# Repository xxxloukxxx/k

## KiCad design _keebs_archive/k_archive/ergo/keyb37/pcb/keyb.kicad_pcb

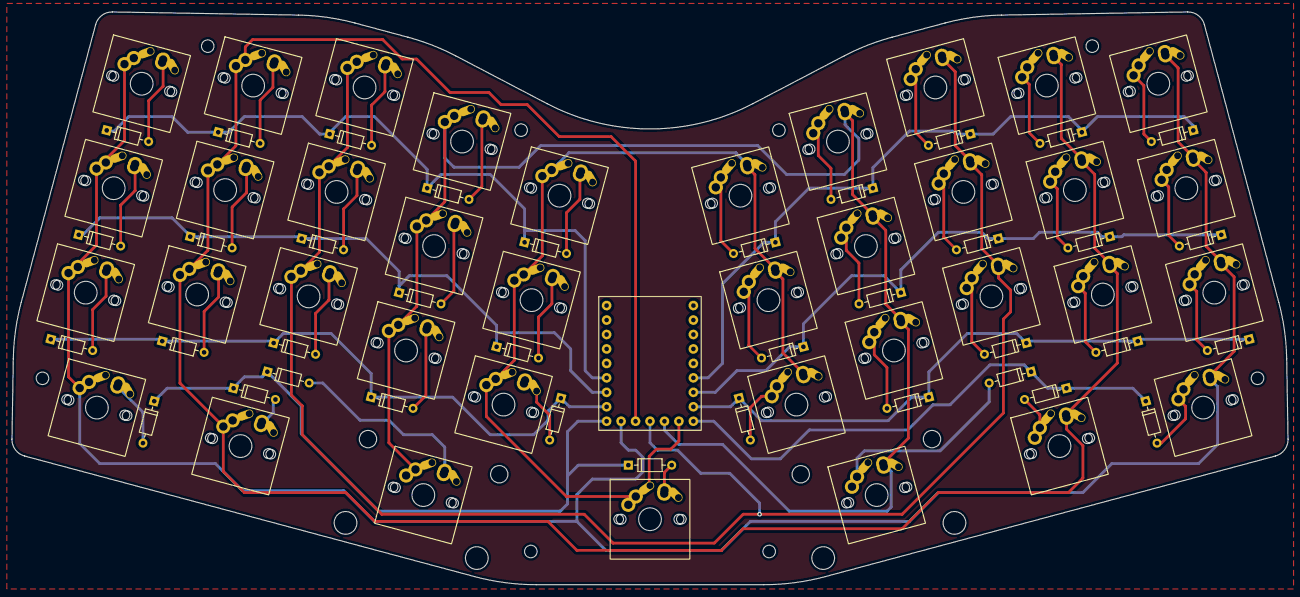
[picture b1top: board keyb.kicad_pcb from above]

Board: 2 copper layers, 224.2 x 100.6 mm, 83 parts (0 on the bottom side), 50 nets.

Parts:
D1, D2, D3, D4, D5, D6, D7, D8, D9, D10, D11, D12, D13, D14, D15, D16, D17, D18, D19, D20, D21, D22, D23, D24, D25, D26, D27, D28, D29, D30, D31, D32, D33, D34, D35, D36, D37: Diode
H1, H2, H3, H4, H5, H6, H7, H8: MountingHole; MountingHole_2.2mm_M2
SW1, SW2, SW3, SW4, SW5, SW6, SW7, SW8, SW9, SW10, SW11, SW12, SW13, SW14, SW15, SW16, SW17, SW18, SW19, SW20, SW21, SW22, SW23, SW24, SW25, SW26, SW27, SW28, SW29, SW30, SW31, SW32, SW34, SW36, SW37: key; MX-5pin
SW33, SW35: key; MX-5pin_stab
U1: RP2040

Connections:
C1: SW1.1, SW10.2, SW11.1, SW20.2, SW21.1, SW30.2, SW31.1, SW37.2, U1.13
C2: SW2.1, SW9.2, SW12.1, SW19.2, SW22.1, SW29.2, SW32.1, SW36.2, U1.12
C3: SW3.1, SW8.2, SW13.1, SW18.2, SW23.1, SW28.2, U1.11
C4: SW4.1, SW7.2, SW14.1, SW17.2, SW24.1, SW27.2, SW33.1, SW35.2, U1.10
C5: SW5.1, SW6.2, SW15.1, SW16.2, SW25.1, SW26.2, SW34.1, U1.9
L1: D1.1, D2.1, D3.1, D4.1, D5.1, U1.17
L2: D11.1, D12.1, D13.1, D14.1, D15.1, U1.16
L3: D21.1, D22.1, D23.1, D24.1, D25.1, U1.15
L4: D31.1, D32.1, D33.1, D34.1, U1.14
L5: D35.1, D36.1, D37.1, U1.8
L6: D26.1, D27.1, D28.1, D29.1, D30.1, U1.7
L7: D16.1, D17.1, D18.1, D19.1, D20.1, U1.6
L8: D6.1, D7.1, D8.1, D9.1, D10.1, U1.5
unnamed: D1.2, SW1.2
unnamed: D2.2, SW2.2
unnamed: D3.2, SW3.2
unnamed: D4.2, SW4.2
unnamed: D5.2, SW5.2
unnamed: D6.2, SW6.1
unnamed: D7.2, SW7.1
unnamed: D8.2, SW8.1
unnamed: D9.2, SW9.1
unnamed: D10.2, SW10.1
unnamed: D11.2, SW11.2
unnamed: D12.2, SW12.2
unnamed: D13.2, SW13.2
unnamed: D14.2, SW14.2
unnamed: D15.2, SW15.2
unnamed: D16.2, SW16.1
unnamed: D17.2, SW17.1
unnamed: D18.2, SW18.1
unnamed: D19.2, SW19.1
unnamed: D20.2, SW20.1
unnamed: D21.2, SW21.2
unnamed: D22.2, SW22.2
unnamed: D23.2, SW23.2
unnamed: D24.2, SW24.2
unnamed: D25.2, SW25.2
unnamed: D26.2, SW26.1
unnamed: D27.2, SW27.1
unnamed: D28.2, SW28.1
unnamed: D29.2, SW29.1
unnamed: D30.2, SW30.1
unnamed: D31.2, SW31.2
unnamed: D32.2, SW32.2
unnamed: D33.2, SW33.2
unnamed: D34.2, SW34.2
unnamed: D35.2, SW35.1
unnamed: D36.2, SW36.1
unnamed: D37.2, SW37.1

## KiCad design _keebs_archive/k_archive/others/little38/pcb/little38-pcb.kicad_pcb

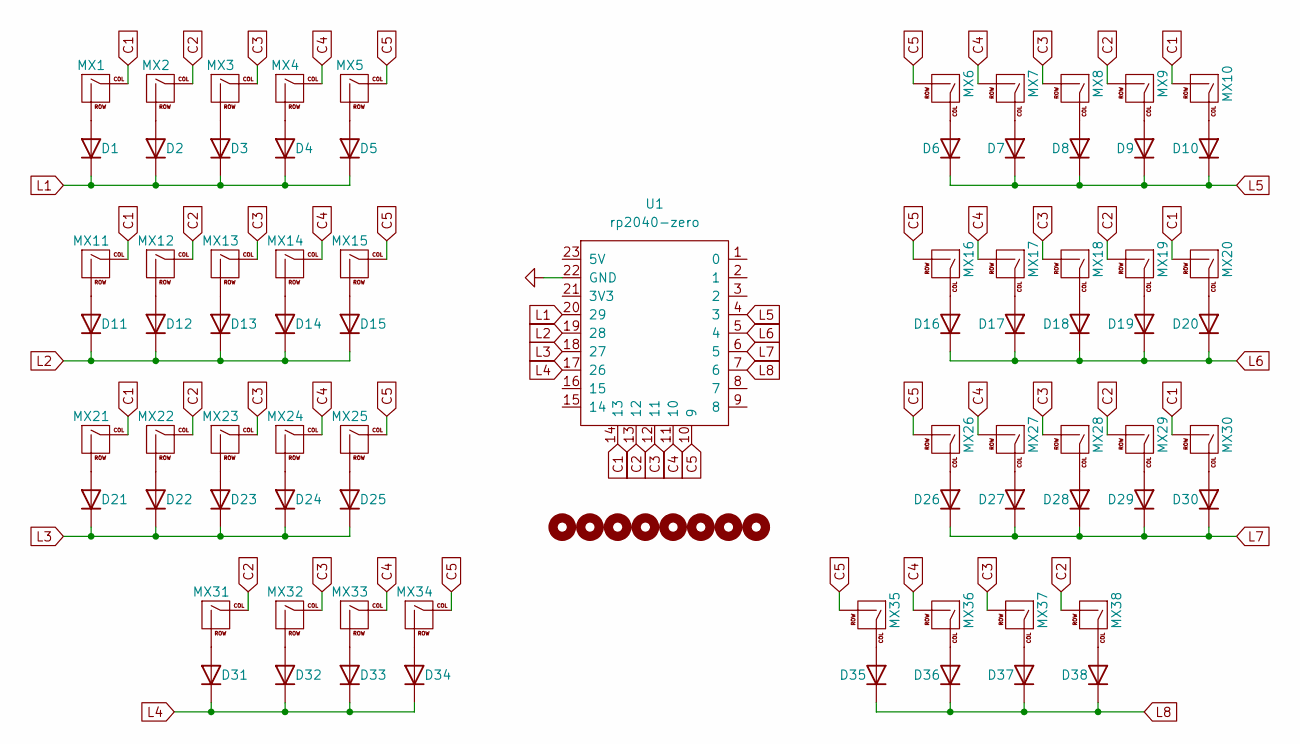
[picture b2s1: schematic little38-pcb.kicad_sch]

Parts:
D1, D2, D3, D4, D5, D6, D7, D8, D9, D10, D11, D12, D13, D14, D15, D16, D17, D18, D19, D20, D21, D22, D23, D24, D25, D26, D27, D28, D29, D30, D31, D32, D33, D34, D35, D36, D37, D38: 1N4148; D_DO-35_SOD27_P7.62mm_Horizontal
H1, H2, H3, H4, H5, H6, H7, H8: MountingHole; MountingHole_2.2mm_M2
MX1, MX2, MX3, MX4, MX5, MX6, MX7, MX8, MX9, MX10, MX11, MX12, MX13, MX14, MX15, MX16, MX17, MX18, MX19, MX20, MX21, MX22, MX23, MX24, MX25, MX26, MX27, MX28, MX29, MX30, MX31, MX32, MX33, MX34, MX35, MX36, MX37, MX38: MX; MX-Alps-Hybrid-1U
U1: rp2040-zero; rp2040-zero-tht

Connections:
C1: MX1.1 (COL), MX10.2 (ROW), MX11.1 (COL), MX20.2 (ROW), MX21.1 (COL), MX30.2 (ROW), U1.14 (13)
C2: MX2.1 (COL), MX9.2 (ROW), MX12.1 (COL), MX19.2 (ROW), MX22.1 (COL), MX29.2 (ROW), MX31.1 (COL), MX38.2 (ROW), U1.13 (12)
C3: MX3.1 (COL), MX8.2 (ROW), MX13.1 (COL), MX18.2 (ROW), MX23.1 (COL), MX28.2 (ROW), MX32.1 (COL), MX37.2 (ROW), U1.12 (11)
C4: MX4.1 (COL), MX7.2 (ROW), MX14.1 (COL), MX17.2 (ROW), MX24.1 (COL), MX27.2 (ROW), MX33.1 (COL), MX36.2 (ROW), U1.11 (10)
C5: MX5.1 (COL), MX6.2 (ROW), MX15.1 (COL), MX16.2 (ROW), MX25.1 (COL), MX26.2 (ROW), MX34.1 (COL), MX35.2 (ROW), U1.10 (9)
GND: U1.22 (GND)
L1: D1.1 (K), D2.1 (K), D3.1 (K), D4.1 (K), D5.1 (K), U1.20 (29)
L2: D11.1 (K), D12.1 (K), D13.1 (K), D14.1 (K), D15.1 (K), U1.19 (28)
L3: D21.1 (K), D22.1 (K), D23.1 (K), D24.1 (K), D25.1 (K), U1.18 (27)
L4: D31.1 (K), D32.1 (K), D33.1 (K), D34.1 (K), U1.17 (26)
L5: D6.1 (K), D7.1 (K), D8.1 (K), D9.1 (K), D10.1 (K), U1.4 (3)
L6: D16.1 (K), D17.1 (K), D18.1 (K), D19.1 (K), D20.1 (K), U1.5 (4)
L7: D26.1 (K), D27.1 (K), D28.1 (K), D29.1 (K), D30.1 (K), U1.6 (5)
L8: D35.1 (K), D36.1 (K), D37.1 (K), D38.1 (K), U1.7 (6)
unnamed: D1.2 (A), MX1.2 (ROW)
unnamed: D2.2 (A), MX2.2 (ROW)
unnamed: D3.2 (A), MX3.2 (ROW)
unnamed: D4.2 (A), MX4.2 (ROW)
unnamed: D5.2 (A), MX5.2 (ROW)
unnamed: D6.2 (A), MX6.1 (COL)
unnamed: D7.2 (A), MX7.1 (COL)
unnamed: D8.2 (A), MX8.1 (COL)
unnamed: D9.2 (A), MX9.1 (COL)
unnamed: D10.2 (A), MX10.1 (COL)
unnamed: D11.2 (A), MX11.2 (ROW)
unnamed: D12.2 (A), MX12.2 (ROW)
unnamed: D13.2 (A), MX13.2 (ROW)
unnamed: D14.2 (A), MX14.2 (ROW)
unnamed: D15.2 (A), MX15.2 (ROW)
unnamed: D16.2 (A), MX16.1 (COL)
unnamed: D17.2 (A), MX17.1 (COL)
unnamed: D18.2 (A), MX18.1 (COL)
unnamed: D19.2 (A), MX19.1 (COL)
unnamed: D20.2 (A), MX20.1 (COL)
unnamed: D21.2 (A), MX21.2 (ROW)
unnamed: D22.2 (A), MX22.2 (ROW)
unnamed: D23.2 (A), MX23.2 (ROW)
unnamed: D24.2 (A), MX24.2 (ROW)
unnamed: D25.2 (A), MX25.2 (ROW)
unnamed: D26.2 (A), MX26.1 (COL)
unnamed: D27.2 (A), MX27.1 (COL)
unnamed: D28.2 (A), MX28.1 (COL)
unnamed: D29.2 (A), MX29.1 (COL)
unnamed: D30.2 (A), MX30.1 (COL)
unnamed: D31.2 (A), MX31.2 (ROW)
unnamed: D32.2 (A), MX32.2 (ROW)
unnamed: D33.2 (A), MX33.2 (ROW)
unnamed: D34.2 (A), MX34.2 (ROW)
unnamed: D35.2 (A), MX35.1 (COL)
unnamed: D36.2 (A), MX36.1 (COL)
unnamed: D37.2 (A), MX37.1 (COL)
unnamed: D38.2 (A), MX38.1 (COL)

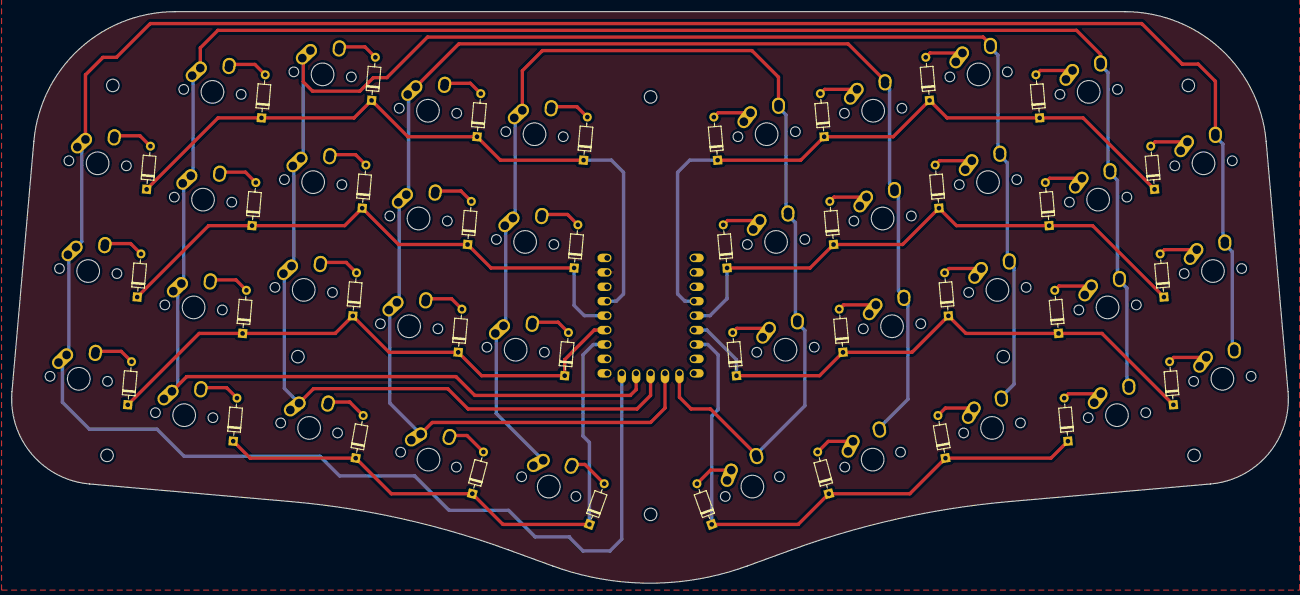
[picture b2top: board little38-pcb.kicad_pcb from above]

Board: 2 copper layers, 224.8 x 100.7 mm, 85 parts (0 on the bottom side), 51 nets.

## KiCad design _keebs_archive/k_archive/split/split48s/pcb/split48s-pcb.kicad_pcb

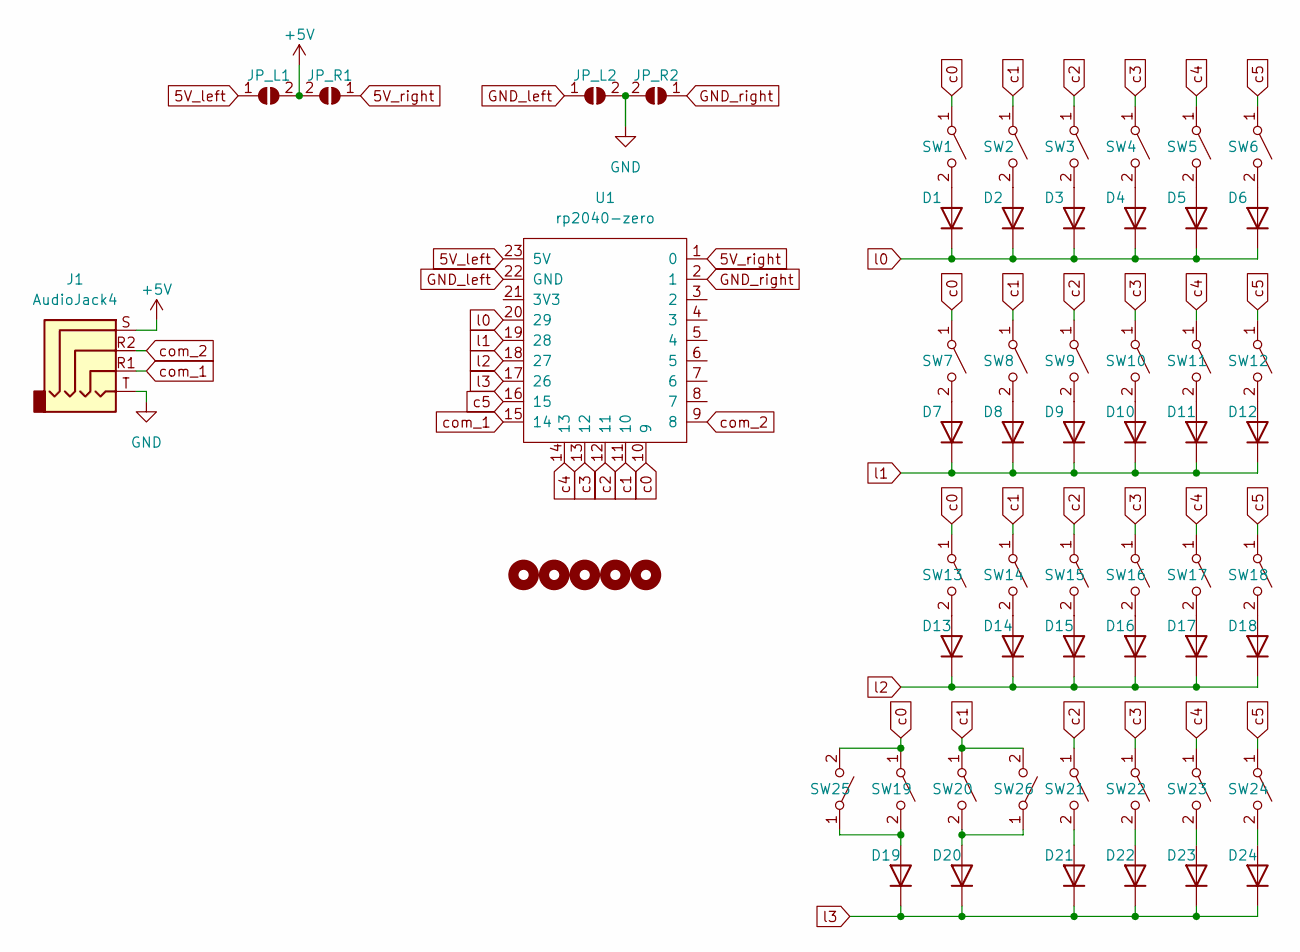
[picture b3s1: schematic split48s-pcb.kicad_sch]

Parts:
D1, D2, D3, D4, D5, D6, D7, D8, D9, D10, D11, D12, D13, D14, D15, D16, D17, D18, D19, D20, D21, D22, D23, D24: 1N4148; D_DO-35_SOD27_P7.62mm_Horizontal
H1, H2, H3, H4, H5: MountingHole; MountingHole_2.2mm_M2
J1: AudioJack4; TRRS-PJ-320A_reversible_2
JP_L1, JP_L2: SolderJumper-2_P1.3mm_Open_RoundedPad1.0x1.5mm
JP_R1, JP_R2: SolderJumper-2_P1.3mm_Open_RoundedPad1.0x1.5mm
SW1, SW2, SW3, SW4, SW5, SW6, SW7, SW8, SW9, SW10, SW11, SW12, SW13, SW14, SW15, SW16, SW17, SW18, SW20, SW22, SW23, SW24: SW_SPST; SW_MX_reversible
SW19, SW21, SW25, SW26: SW_SPST; SW_MX_reversible_2
U1: rp2040-zero; rp2040-zero-tht

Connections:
5V_left: JP_L1.1 (A), U1.23 (5V)
5V_right: JP_R1.1 (A), U1.1 (0)
+5V: J1.S, JP_L1.2 (B), JP_R1.2 (B)
GND: J1.T, JP_L2.2 (B), JP_R2.2 (B)
GND_left: JP_L2.1 (A), U1.22 (GND)
GND_right: JP_R2.1 (A), U1.2 (1)
unnamed: D1.2 (A), SW1.2 (B)
unnamed: D2.2 (A), SW2.2 (B)
unnamed: D3.2 (A), SW3.2 (B)
unnamed: D4.2 (A), SW4.2 (B)
unnamed: D5.2 (A), SW5.2 (B)
unnamed: D6.2 (A), SW6.2 (B)
unnamed: D7.2 (A), SW7.2 (B)
unnamed: D8.2 (A), SW8.2 (B)
unnamed: D9.2 (A), SW9.2 (B)
unnamed: D10.2 (A), SW10.2 (B)
unnamed: D11.2 (A), SW11.2 (B)
unnamed: D12.2 (A), SW12.2 (B)
unnamed: D13.2 (A), SW13.2 (B)
unnamed: D14.2 (A), SW14.2 (B)
unnamed: D15.2 (A), SW15.2 (B)
unnamed: D16.2 (A), SW16.2 (B)
unnamed: D17.2 (A), SW17.2 (B)
unnamed: D18.2 (A), SW18.2 (B)
unnamed: D19.2 (A), SW19.2 (B), SW25.1 (A)
unnamed: D20.2 (A), SW20.2 (B), SW26.1 (A)
unnamed: D21.2 (A), SW21.2 (B)
unnamed: D22.2 (A), SW22.2 (B)
unnamed: D23.2 (A), SW23.2 (B)
unnamed: D24.2 (A), SW24.2 (B)
c0: SW1.1 (A), SW7.1 (A), SW13.1 (A), SW19.1 (A), SW25.2 (B), U1.10 (9)
c1: SW2.1 (A), SW8.1 (A), SW14.1 (A), SW20.1 (A), SW26.2 (B), U1.11 (10)
c2: SW3.1 (A), SW9.1 (A), SW15.1 (A), SW21.1 (A), U1.12 (11)
c3: SW4.1 (A), SW10.1 (A), SW16.1 (A), SW22.1 (A), U1.13 (12)
c4: SW5.1 (A), SW11.1 (A), SW17.1 (A), SW23.1 (A), U1.14 (13)
c5: SW6.1 (A), SW12.1 (A), SW18.1 (A), SW24.1 (A), U1.16 (15)
com_1: J1.R1, U1.15 (14)
com_2: J1.R2, U1.9 (8)
l0: D1.1 (K), D2.1 (K), D3.1 (K), D4.1 (K), D5.1 (K), D6.1 (K), U1.20 (29)
l1: D7.1 (K), D8.1 (K), D9.1 (K), D10.1 (K), D11.1 (K), D12.1 (K), U1.19 (28)
l2: D13.1 (K), D14.1 (K), D15.1 (K), D16.1 (K), D17.1 (K), D18.1 (K), U1.18 (27)
l3: D19.1 (K), D20.1 (K), D21.1 (K), D22.1 (K), D23.1 (K), D24.1 (K), U1.17 (26)

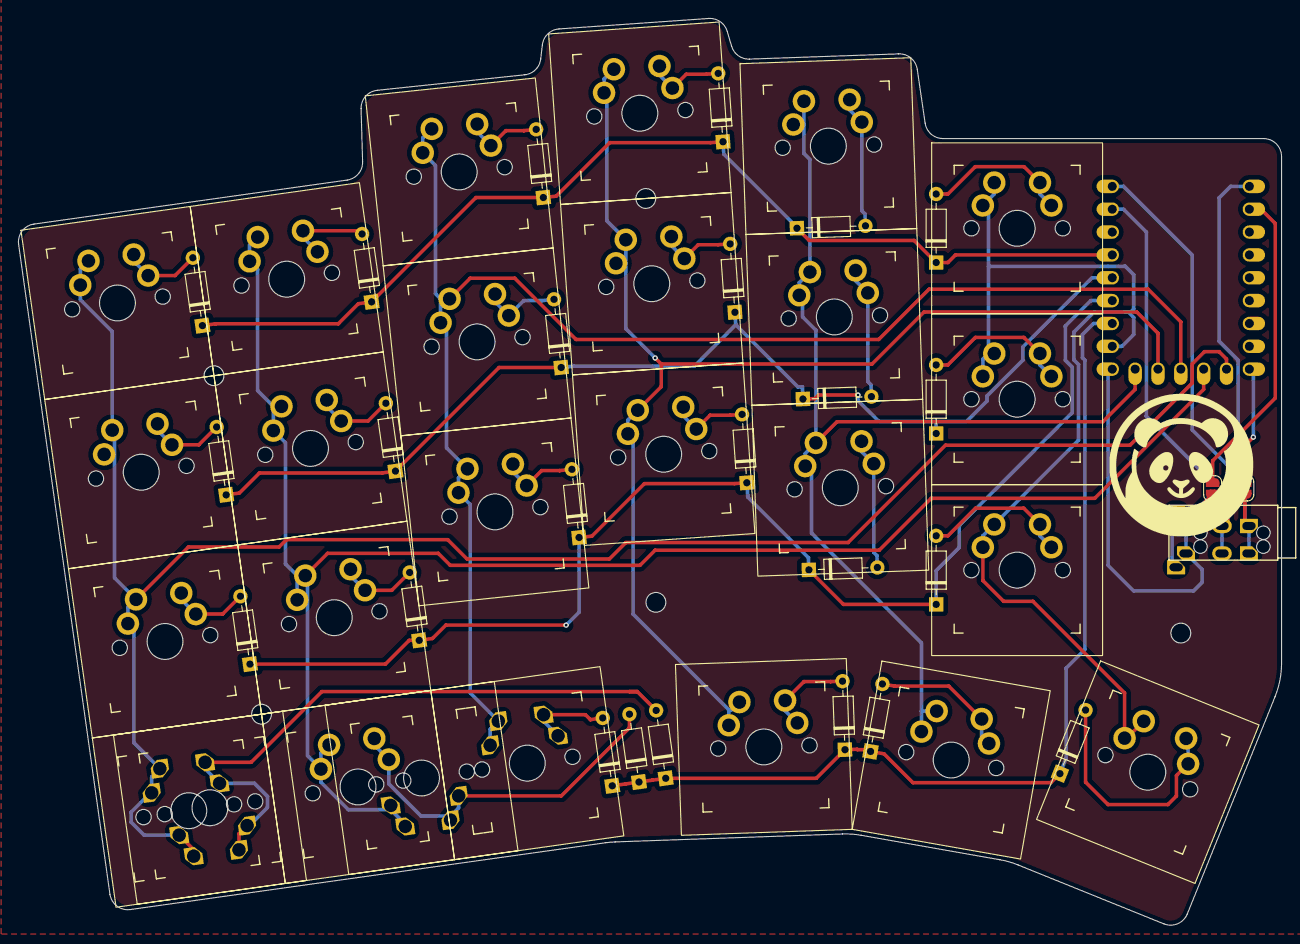
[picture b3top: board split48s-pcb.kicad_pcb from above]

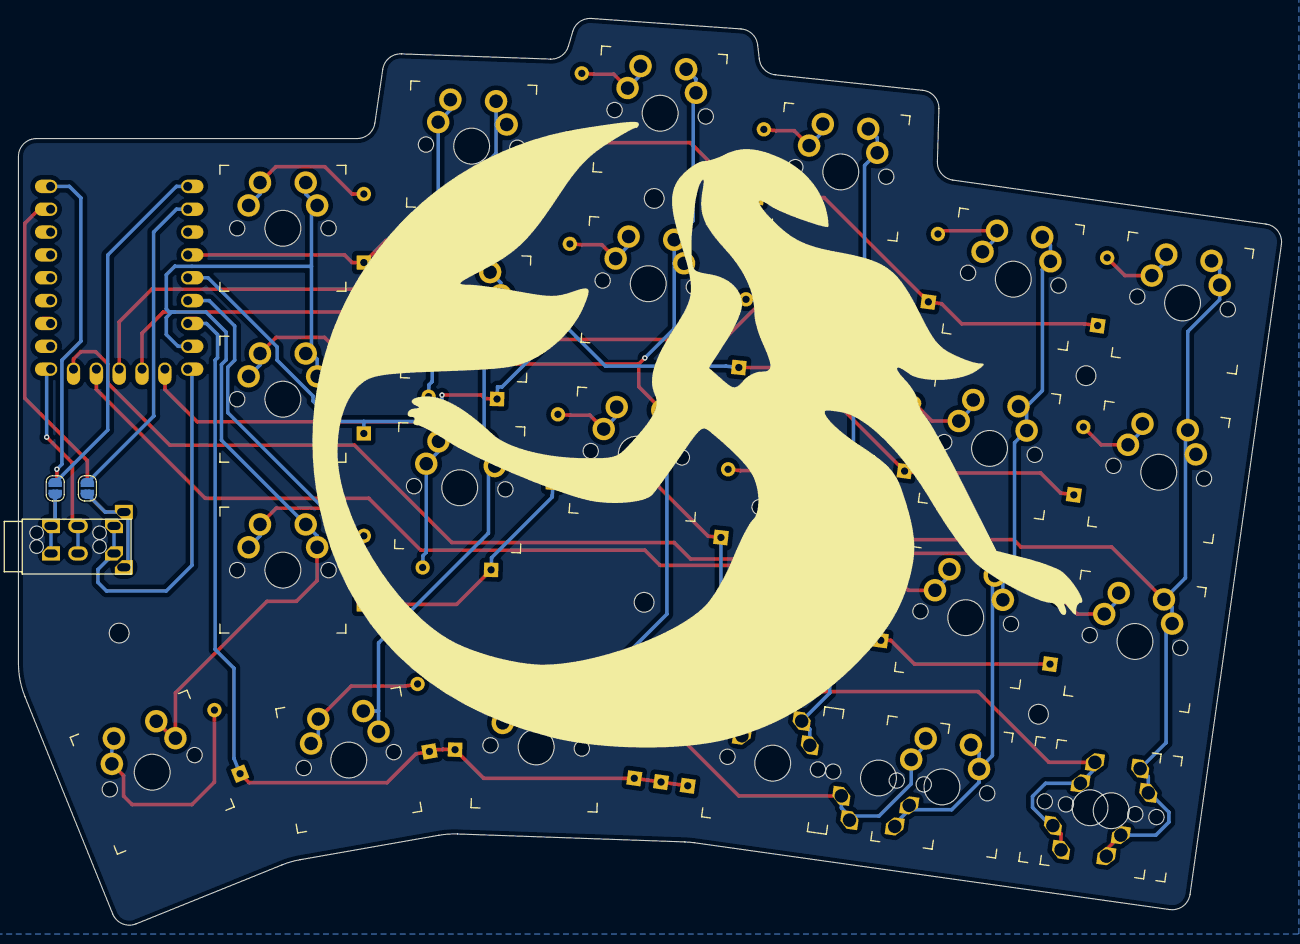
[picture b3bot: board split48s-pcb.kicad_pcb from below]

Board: 2 copper layers, 140.4 x 100.8 mm, 61 parts (2 on the bottom side), 42 nets.

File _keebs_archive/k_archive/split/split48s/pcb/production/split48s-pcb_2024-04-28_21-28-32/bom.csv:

Designator,Footprint,Quantity,Value,LCSC Part #
"D1, D10, D11, D12, D13, D14, D15, D16, D17, D18, D19, D2, D20, D21, D22, D23, D24, D3, D4, D5, D6, D7, D8, D9",D_DO-35_SOD27_P7.62mm_Horizontal,24,1N4148,
"H1, H2, H3, H4, H5",MountingHole_2.2mm_M2,5,MountingHole,
J1,TRRS-PJ-320A_reversible_2,1,AudioJack4,
"JP_L1, JP_L2, JP_R1, JP_R2",SolderJumper-2_P1.3mm_Open_RoundedPad1.0x1.5mm,4,~,
"SW1, SW10, SW11, SW12, SW13, SW14, SW15, SW16, SW17, SW18, SW2, SW20, SW22, SW23, SW24, SW3, SW4, SW5, SW6, SW7, SW8, SW9",SW_MX_reversible,22,SW_SPST,
"SW19, SW21, SW25, SW26",SW_MX_reversible_2,4,SW_SPST,
U1,rp2040-zero-tht,1,rp2040-zero,

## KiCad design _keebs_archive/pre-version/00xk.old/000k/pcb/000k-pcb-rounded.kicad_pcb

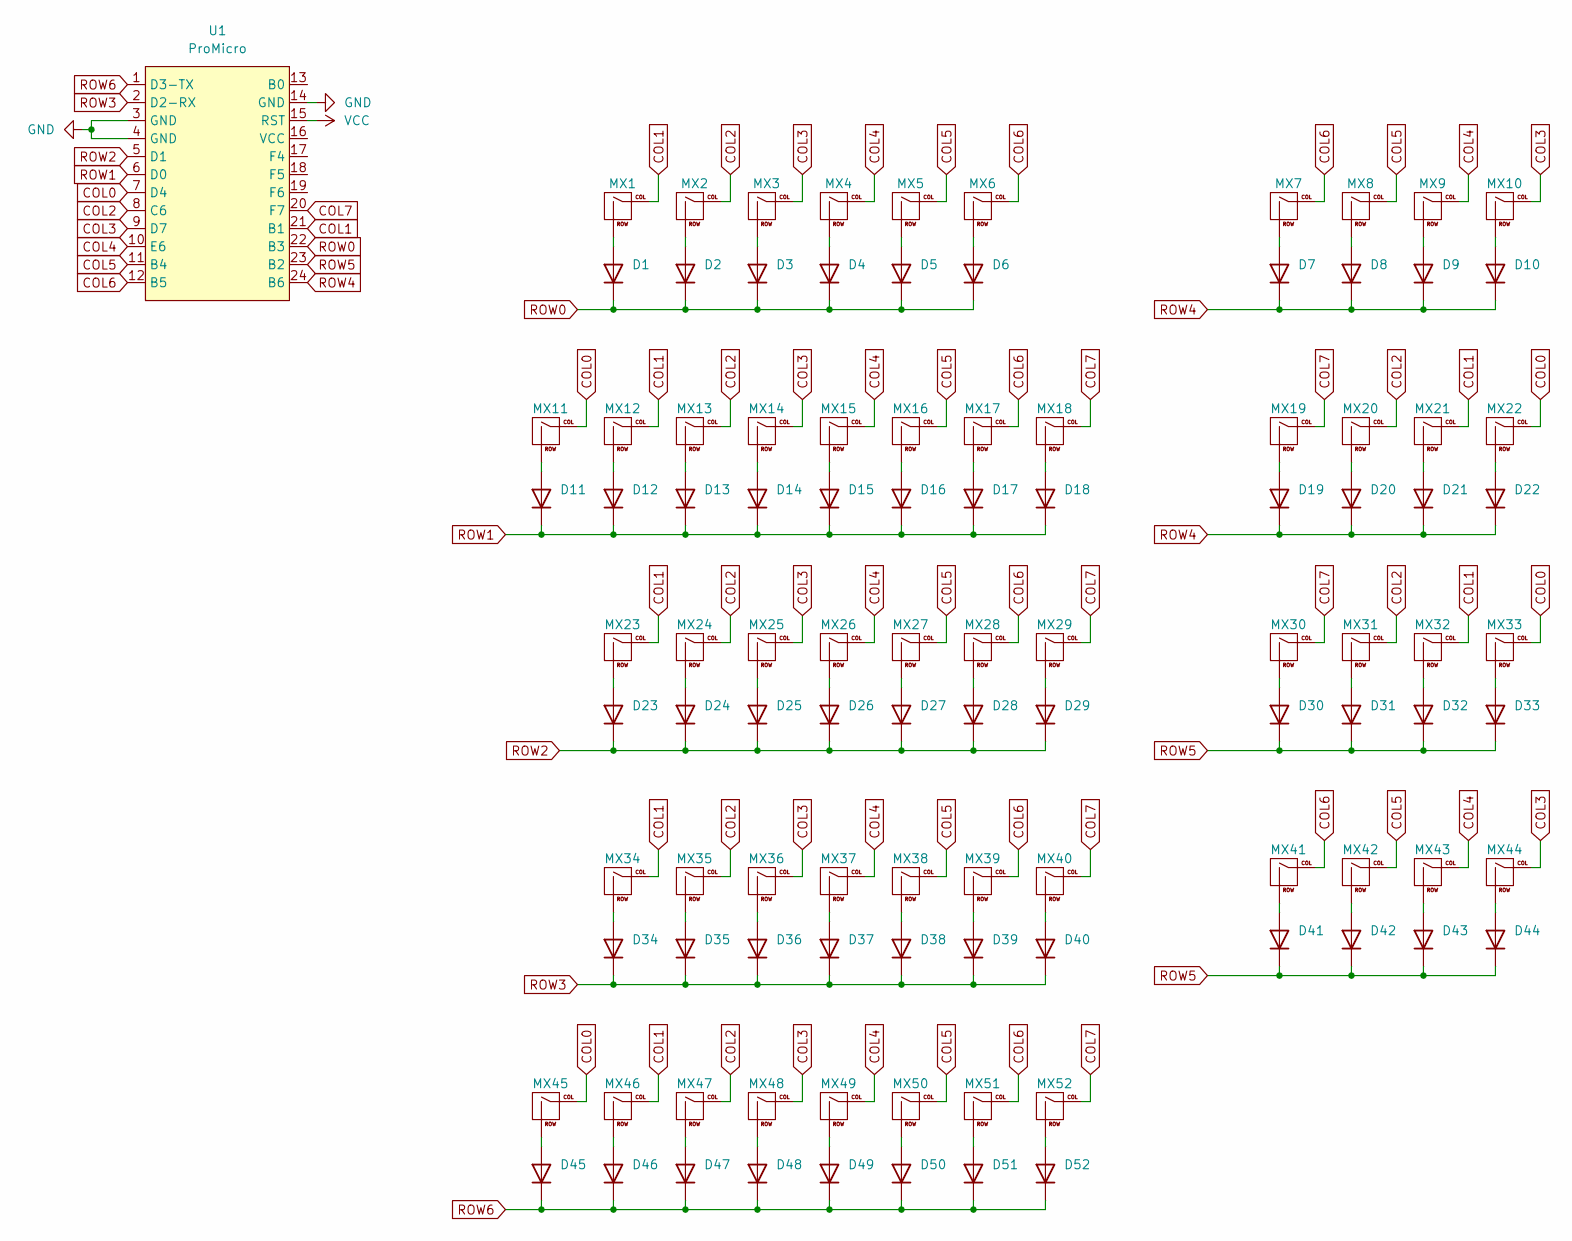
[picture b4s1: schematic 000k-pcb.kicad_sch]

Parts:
D1, D2, D3, D4, D5, D6, D7, D8, D9, D10, D11, D12, D13, D14, D15, D16, D17, D18, D19, D20, D21, D22, D23, D24, D25, D26, D27, D28, D29, D30, D31, D32, D33, D34, D35, D36, D37, D38, D39, D40, D41, D42, D43, D44, D45, D46, D47, D48, D49, D50, D51, D52: 1N4148; D_DO-35_SOD27_P7.62mm_Horizontal
MX1, MX2, MX3, MX4, MX5, MX6, MX7, MX8, MX9, MX10, MX11, MX12, MX13, MX14, MX15, MX16, MX17, MX18, MX19, MX20, MX21, MX22, MX24, MX25, MX26, MX27, MX28, MX29, MX30, MX31, MX32, MX35, MX36, MX37, MX38, MX39, MX40, MX41, MX42, MX43, MX46, MX51: MX; MX-Solderable-1U
MX23, MX44, MX45, MX47, MX50, MX52: MX; MX-Solderable-1.25U
MX33, MX34: MX; MX-Solderable-1.75U
MX48: MX; MX-Solderable-2.75U-ReversedStabilizers
MX49: MX; MX-Solderable-2.25U-ReversedStabilizers
U1: ProMicro; ProMicro_USBup

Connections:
COL0: MX11.1 (COL), MX22.1 (COL), MX33.1 (COL), MX45.1 (COL), U1.7 (D4)
COL1: MX1.1 (COL), MX12.1 (COL), MX21.1 (COL), MX23.1 (COL), MX32.1 (COL), MX34.1 (COL), MX46.1 (COL), U1.21 (B1)
COL2: MX2.1 (COL), MX13.1 (COL), MX20.1 (COL), MX24.1 (COL), MX31.1 (COL), MX35.1 (COL), MX47.1 (COL), U1.8 (C6)
COL3: MX3.1 (COL), MX10.1 (COL), MX14.1 (COL), MX25.1 (COL), MX36.1 (COL), MX44.1 (COL), MX48.1 (COL), U1.9 (D7)
COL4: MX4.1 (COL), MX9.1 (COL), MX15.1 (COL), MX26.1 (COL), MX37.1 (COL), MX43.1 (COL), MX49.1 (COL), U1.10 (E6)
COL5: MX5.1 (COL), MX8.1 (COL), MX16.1 (COL), MX27.1 (COL), MX38.1 (COL), MX42.1 (COL), MX50.1 (COL), U1.11 (B4)
COL6: MX6.1 (COL), MX7.1 (COL), MX17.1 (COL), MX28.1 (COL), MX39.1 (COL), MX41.1 (COL), MX51.1 (COL), U1.12 (B5)
COL7: MX18.1 (COL), MX19.1 (COL), MX29.1 (COL), MX30.1 (COL), MX40.1 (COL), MX52.1 (COL), U1.20 (F7)
GND: U1.3 (GND), U1.4 (GND), U1.14 (GND)
unnamed: D1.2 (A), MX1.2 (ROW)
unnamed: D2.2 (A), MX2.2 (ROW)
unnamed: D3.2 (A), MX3.2 (ROW)
unnamed: D4.2 (A), MX4.2 (ROW)
unnamed: D5.2 (A), MX5.2 (ROW)
unnamed: D6.2 (A), MX6.2 (ROW)
unnamed: D7.2 (A), MX7.2 (ROW)
unnamed: D8.2 (A), MX8.2 (ROW)
unnamed: D9.2 (A), MX9.2 (ROW)
unnamed: D10.2 (A), MX10.2 (ROW)
unnamed: D11.2 (A), MX11.2 (ROW)
unnamed: D12.2 (A), MX12.2 (ROW)
unnamed: D13.2 (A), MX13.2 (ROW)
unnamed: D14.2 (A), MX14.2 (ROW)
unnamed: D15.2 (A), MX15.2 (ROW)
unnamed: D16.2 (A), MX16.2 (ROW)
unnamed: D17.2 (A), MX17.2 (ROW)
unnamed: D18.2 (A), MX18.2 (ROW)
unnamed: D19.2 (A), MX19.2 (ROW)
unnamed: D20.2 (A), MX20.2 (ROW)
unnamed: D21.2 (A), MX21.2 (ROW)
unnamed: D22.2 (A), MX22.2 (ROW)
unnamed: D23.2 (A), MX23.2 (ROW)
unnamed: D24.2 (A), MX24.2 (ROW)
unnamed: D25.2 (A), MX25.2 (ROW)
unnamed: D26.2 (A), MX26.2 (ROW)
unnamed: D27.2 (A), MX27.2 (ROW)
unnamed: D28.2 (A), MX28.2 (ROW)
unnamed: D29.2 (A), MX29.2 (ROW)
unnamed: D30.2 (A), MX30.2 (ROW)
unnamed: D31.2 (A), MX31.2 (ROW)
unnamed: D32.2 (A), MX32.2 (ROW)
unnamed: D33.2 (A), MX33.2 (ROW)
unnamed: D34.2 (A), MX34.2 (ROW)
unnamed: D35.2 (A), MX35.2 (ROW)
unnamed: D36.2 (A), MX36.2 (ROW)
unnamed: D37.2 (A), MX37.2 (ROW)
unnamed: D38.2 (A), MX38.2 (ROW)
unnamed: D39.2 (A), MX39.2 (ROW)
unnamed: D40.2 (A), MX40.2 (ROW)
unnamed: D41.2 (A), MX41.2 (ROW)
unnamed: D42.2 (A), MX42.2 (ROW)
unnamed: D43.2 (A), MX43.2 (ROW)
unnamed: D44.2 (A), MX44.2 (ROW)
unnamed: D45.2 (A), MX45.2 (ROW)
unnamed: D46.2 (A), MX46.2 (ROW)
unnamed: D47.2 (A), MX47.2 (ROW)
unnamed: D48.2 (A), MX48.2 (ROW)
unnamed: D49.2 (A), MX49.2 (ROW)
unnamed: D50.2 (A), MX50.2 (ROW)
unnamed: D51.2 (A), MX51.2 (ROW)
unnamed: D52.2 (A), MX52.2 (ROW)
ROW0: D1.1 (K), D2.1 (K), D3.1 (K), D4.1 (K), D5.1 (K), D6.1 (K), U1.22 (B3)
ROW1: D11.1 (K), D12.1 (K), D13.1 (K), D14.1 (K), D15.1 (K), D16.1 (K), D17.1 (K), D18.1 (K), U1.6 (D0)
ROW2: D23.1 (K), D24.1 (K), D25.1 (K), D26.1 (K), D27.1 (K), D28.1 (K), D29.1 (K), U1.5 (D1)
ROW3: D34.1 (K), D35.1 (K), D36.1 (K), D37.1 (K), D38.1 (K), D39.1 (K), D40.1 (K), U1.2 (D2-RX)
ROW4: D7.1 (K), D8.1 (K), D9.1 (K), D10.1 (K), D19.1 (K), D20.1 (K), D21.1 (K), D22.1 (K), U1.24 (B6)
ROW5: D30.1 (K), D31.1 (K), D32.1 (K), D33.1 (K), D41.1 (K), D42.1 (K), D43.1 (K), D44.1 (K), U1.23 (B2)
ROW6: D45.1 (K), D46.1 (K), D47.1 (K), D48.1 (K), D49.1 (K), D50.1 (K), D51.1 (K), D52.1 (K), U1.1 (D3-TX)
VCC: U1.15 (RST)

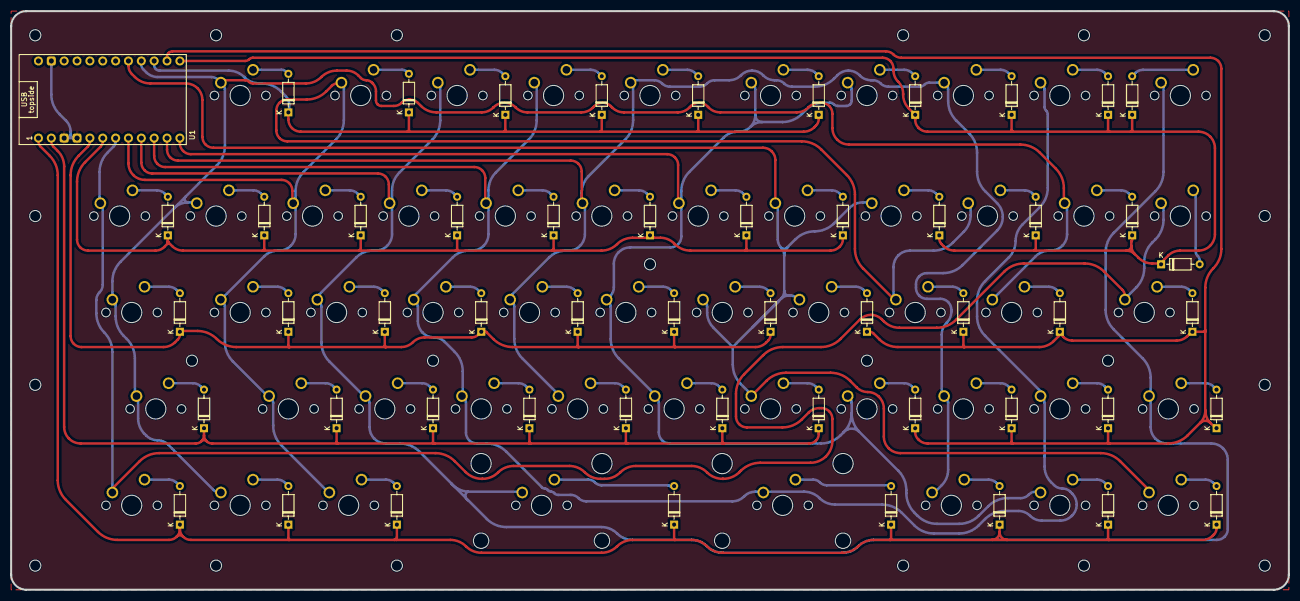
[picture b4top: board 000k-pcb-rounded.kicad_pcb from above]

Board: 2 copper layers, 252.4 x 114.3 mm, 105 parts (0 on the bottom side), 68 nets.

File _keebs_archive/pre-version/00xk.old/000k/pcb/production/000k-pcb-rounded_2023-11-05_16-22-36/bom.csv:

Designator,Footprint,Quantity,Value,LCSC Part #
"D1, D10, D11, D12, D13, D14, D15, D16, D17, D18, D19, D2, D20, D21, D22, D23, D24, D25, D26, D27, D28, D29, D3, D30, D31, D32, D33, D34, D35, D36, D37, D38, D39, D4, D40, D41, D42, D43, D44, D45, D46, D47, D48, D49, D5, D50, D51, D52, D6, D7, D8, D9",D_DO-35_SOD27_P7.62mm_Horizontal,52,1N4148,
"MX1, MX10, MX11, MX12, MX13, MX14, MX15, MX16, MX17, MX18, MX19, MX2, MX20, MX21, MX22, MX24, MX25, MX26, MX27, MX28, MX29, MX3, MX30, MX31, MX32, MX35, MX36, MX37, MX38, MX39, MX4, MX40, MX41, MX42, MX43, MX46, MX5, MX51, MX6, MX7, MX8, MX9",MX-Solderable-1U,42,MX,
"MX23, MX44, MX45, MX47, MX50, MX52",MX-Solderable-1.25U,6,MX,
"MX33, MX34",MX-Solderable-1.75U,2,MX,
MX48,MX-Solderable-2.75U-ReversedStabilizers,1,MX,
MX49,MX-Solderable-2.25U-ReversedStabilizers,1,MX,
